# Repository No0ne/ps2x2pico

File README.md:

# ps2x2pico
USB keyboard/mouse to PS/2 interface converter using a Raspberry Pi Pico

| | | | |
|-|-|-|-|

Keyboard only (incl. PC-XT) variant: https://github.com/No0ne/ps2pico  
There is also an alternative ps2pico firmware for the PC-XT and ps2x2pico hardware: [ps2pico-XT-alt.uf2](https://github.com/No0ne/ps2pico/releases/tag/2.2)

Additional excellent documentation by Ray: https://minuszerodegrees.net/keyboard/ps2x2pico.htm

[PicoMiteVGA](https://geoffg.net/picomitevga.html) variant: https://github.com/No0ne/hid2cdc

[PiKVM](https://pikvm.org) integration:
* https://docs.pikvm.org/pico_hid/
* https://docs.pikvm.org/pico_hid_bridge/

[ITX-Llama](https://www.vogons.org/viewtopic.php?t=93480) integration:
https://github.com/eivindbohler/itxllama

# Usage
* Download `ps2x2pico.uf2` from https://github.com/No0ne/ps2x2pico/releases
* Copy `ps2x2pico.uf2` to your Pi Pico by pressing BOOTSEL before pluggging in.
* 3.3V/5V conversion is done using a bi-directional level shifter: https://learn.sparkfun.com/tutorials/bi-directional-logic-level-converter-hookup-guide/
* Afterwards connect a USB keyboard and/or mouse using an OTG-adapter and optional USB hub.
* Also works with wireless keyboards and mice with a dedicated USB receiver.

⚠️ Please note that some older motherboards have non-resettable fuses rated
under 300mA.

**Check the power consumption of your keyboard/mouse/hub first before plugging
in!**

⚠️ Do not assume wire colors will match cables depicted in photos. Double-check
your pinout with a multimeter.

# PS/2 passthru
If you also want to use a real PS/2 keyboard and mouse together with your USB devices you can mount another level shifter on top of the pico. These two ports work as PS/2 inputs and are passed through to the PS/2 output ports.
* GPIO3 LV1 - keyboard data
* GPIO4 LV2 - keyboard clock
* GPIO5 LV - 3.3V pull-up
* GND - GND
* GPIO6 LV3 - mouse data
* GPIO7 LV4 - mouse clock

Don't forget to wire HV to 5V and your PS/2 sockets to power the connected PS/2 devices.

PS/2 passthru is especially useful with the PiKVM [Pico HID](https://docs.pikvm.org/pico_hid/) or [Pico HID Bridge](https://docs.pikvm.org/pico_hid_bridge/) as you can continue using your existing peripherals.  
⚠️ Please note that the [UF2 from PiKVM](https://github.com/pikvm/kvmd/releases) uses different GPIOs due to jumper pins:
* GPIO26 LV1 - keyboard data
* GPIO27 LV2 - keyboard clock
* GPIO16 LV3 - mouse data
* GPIO17 LV4 - mouse clock

Don't forget to wire LV to 3.3V and GND to GND separately as the level shifter does not fit directly on top of the pico. 

# Troubleshooting
You can hook up a USB serial adapter to **GPIO0** for additional debugging output. The serial settings are **115200** baud, **8** data bits and **no parity**. You can also use another Pico running the [pico-uart-bridge](https://github.com/Noltari/pico-uart-bridge) for this.

⚠️ If you have a **YD-RP2040** (see silkscreen on back of board if unsure) and
are not using a USB hub with its own power supply, you need to bridge two pads
of the diode pair near the USB-C port as seen here:

# Build

Install needed libraries and tools:

```sh
sudo apt install cmake gcc-arm-none-eabi build-essential pkg-config libusb-1.0-0-dev libusb-1.0-0
```

Get the Raspberry Pi Pico SDK version 1.5.1:

```sh
git clone https://github.com/raspberrypi/pico-sdk
export PICO_SDK_PATH=/path/to/pico-sdk
cd $PICO_SDK_PATH
git checkout 1.5.1
git submodule update --init
```

Update to the latest TinyUSB release 0.17.0:
```sh
cd $PICO_SDK_PATH/lib/tinyusb
git checkout 0.17.0
```

Generate the UF2 file:
```sh
cd /path/to/ps2x2pico
mkdir build
cd build
cmake ..
make
```

# Case

There are two case versions for this project, one for the hat variant in `freecad/` and one for the level shifter version in `openscad/`.

## Level shifter version

The case is snap fit and doesn't require any fasteners. You can print it as is using `ps2x2pico_case.stl` in your slicer but various customisation options are included in the underlying OpenSCAD model `ps2x2pico_case.scad` should you need them. This allows you to adjust tolerances or clearances of the height of the case and the various holes and support posts.

Note that when opening the case in OpenSCAD the [BOSL2](https://github.com/BelfrySCAD/BOSL2) library is required.

# Resources
* https://github.com/No0ne/ps2pico
* https://wiki.osdev.org/PS/2_Keyboard
* https://wiki.osdev.org/PS/2_Mouse
* https://wiki.osdev.org/Mouse_Input
* https://wiki.osdev.org/%228042%22_PS/2_Controller
* http://www-ug.eecg.toronto.edu/msl/nios_devices/datasheets/PS2%20Keyboard%20Protocol.htm
* http://www-ug.eecg.utoronto.ca/desl/nios_devices_SoC/datasheets/PS2%20Mouse%20Protocol.htm
* Archive.org links for the dead links in the pages above
  * [Main page PS/2 Keyboard Protocol](https://web.archive.org/web/20160414014033if_/http://www.computer-engineering.org/ps2keyboard/)
    * [Scan code set 1](https://web.archive.org/web/20160410193756if_/http://www.computer-engineering.org/ps2keyboard/scancodes1.html)
    * [Scan code set 2](https://web.archive.org/web/20160414030011if_/http://www.computer-engineering.org/ps2keyboard/scancodes2.html)
    * [Scan code set 3](https://web.archive.org/web/20160410184920if_/http://www.computer-engineering.org/ps2keyboard/scancodes3.html)
  * [Main page PS/2 Mouse Protocol](https://web.archive.org/web/20160414013310if_/http://www.computer-engineering.org/ps2mouse/)

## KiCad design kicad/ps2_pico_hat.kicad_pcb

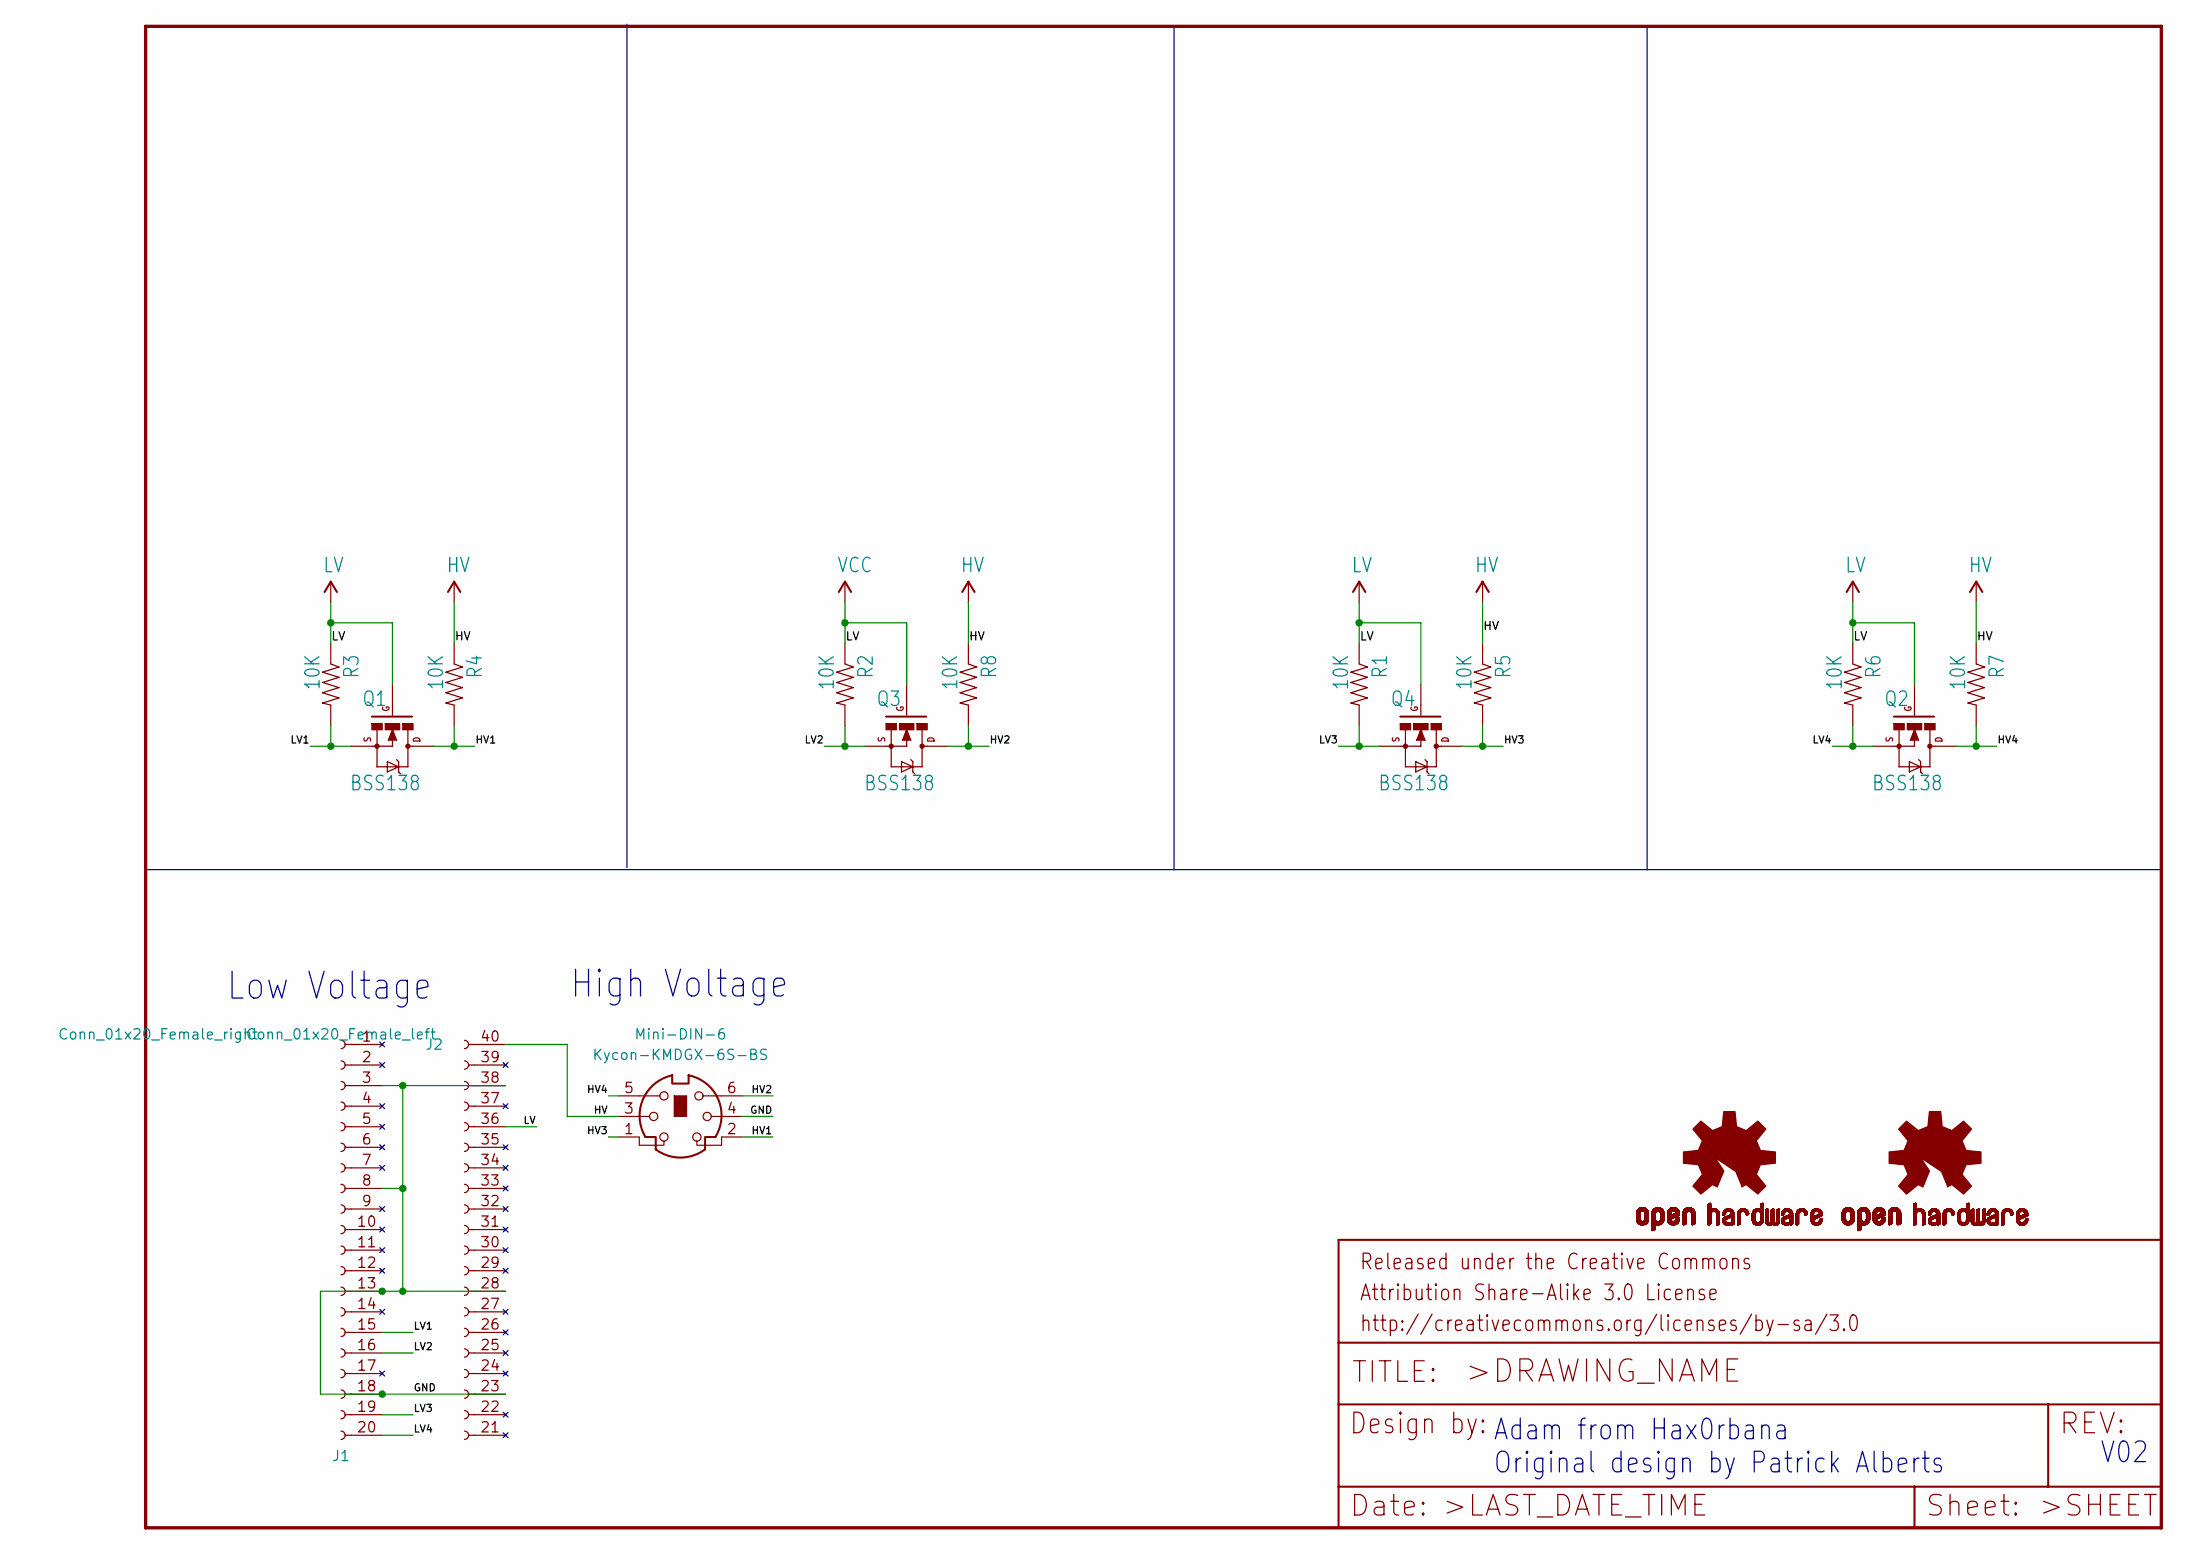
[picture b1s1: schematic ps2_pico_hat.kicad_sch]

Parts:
J1: Conn_01x20_Female_left; PinSocket_1x20_P2.54mm_Vertical
J2: Conn_01x20_Female_right; PinSocket_1x20_P2.54mm_Vertical
LOGO1, LOGO2: OSHW-LOGOS; OSHW-LOGO-S
Mini-DIN-6: Kycon-KMDGX-6S-BS; KMDGX-6S-BS
Q1, Q2, Q3, Q4: BSS138; SOT23-3
R1, R2, R3, R4, R5, R6, R7, R8: 10K; 0603-RES

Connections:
/GND: J1.3 (GND), J1.8 (GND), J1.13 (GND), J1.18 (GND), J2.23 (GND), J2.28 (GND), J2.38 (GND), Mini-DIN-6.4
/HV1: Mini-DIN-6.2, Q1.3 (D), R4.2
/HV2: Mini-DIN-6.6, Q3.3 (D), R8.2
/HV3: Mini-DIN-6.1, Q4.3 (D), R5.2
/HV4: Mini-DIN-6.5, Q2.3 (D), R7.2
/LV1: J1.15, Q1.2 (S), R3.2
/LV2: J1.16, Q3.2 (S), R2.2
/LV3: J1.19, Q4.2 (S), R1.2
/LV4: J1.20, Q2.2 (S), R6.2
HV: J2.40, Mini-DIN-6.3, R4.1, R5.1, R7.1, R8.1
LV: J2.36 (LV), Q1.1 (G), Q2.1 (G), Q3.1 (G), Q4.1 (G), R1.1, R2.1, R3.1, R6.1

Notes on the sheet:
Low Voltage
V02
Adam from Hax0rbana Original design by Patrick Alberts
High Voltage

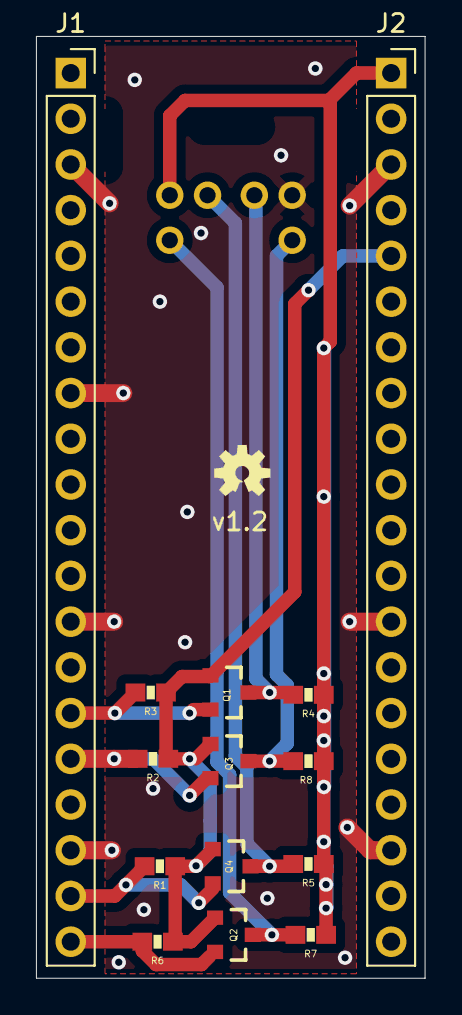
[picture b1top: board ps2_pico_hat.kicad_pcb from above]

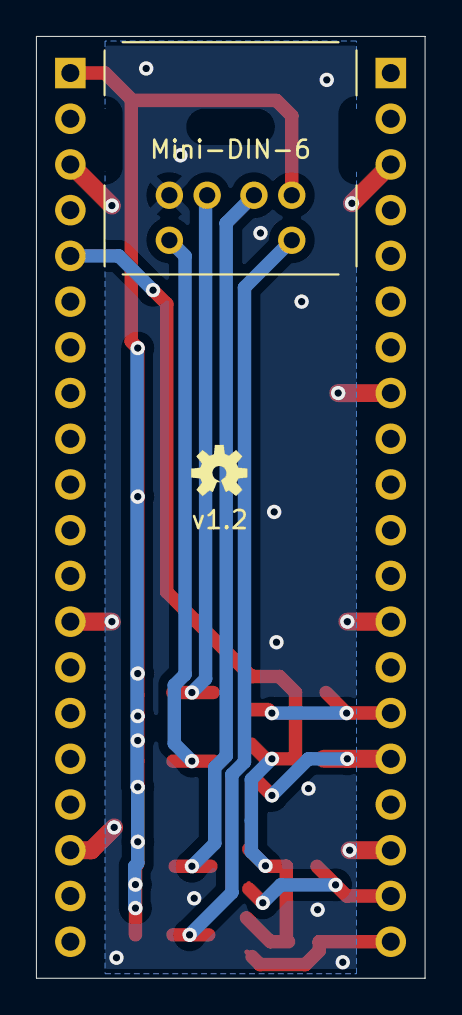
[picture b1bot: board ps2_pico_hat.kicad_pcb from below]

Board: 2 copper layers, 21.6 x 52.3 mm, 17 parts (2 on the bottom side), 11 nets.

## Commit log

2022-08-23 pico_project.py -x -f pio ps2x2pico
2022-08-23 tinyusb
2022-08-24 tinyusb compiled
2022-09-10 blink test
2022-09-10 README.md
2022-09-10 import from ps2pico
2022-09-10 keyboard testing
2022-09-10 keyboard working
2022-09-11 alpha-0.1 - mouse wheel not working + lots of cleanup needed
2022-09-11 alpha-0.2 - mouse wheel working, cleanup still needed
2022-09-13 Logitech Unifying receiver tested
2022-09-13 mousewheel debugging
2022-09-27 updated via ps2pico
2022-11-05 fix timing issue on NuXTv2
2022-11-11 Started implementing a more compatible ps2 mouse emulation
2022-11-12 more compatible ps2 mouse emulation
2022-11-13 ps2ports.pio
2022-11-13 develop sdk
2022-12-04 transmitting via pio
2022-12-07 PIOs tested successfully
2022-12-11 split send & receive state machines
2022-12-13 still something broken
2022-12-14 works on P3B-F
2022-12-14 NuXTv2 working
2022-12-17 receive timing captured from real keyboard
2022-12-17 combine send & receive state machines
2022-12-17 mouse testing
2022-12-18 pio testing nearly finished
2022-12-18 ready for testing
2022-12-22 send 0xaa after blinking
2023-01-26 Working on seperating transciever logic into seperate component.
2023-01-28 More fixes.
2023-01-28 Fixed documentation and removed bad comments.
2023-02-04 fix scroll wheel up represenation
    There are only 4 bit available for scroll wheel movement, not 8 bit.
    Use (0x10 - z) to get the proper 4 bit complement.
2023-02-05 add support for mouse button 4 & 5
2023-04-28 update keyboard prev_rpt atomically
    Modifying previous HID report during parsing of current HID report may
    lead to spurious PS/2 key presses: some HID devices report 2nd key in
    a combo by shifting the report to the right and saving that key in the
    1st report slot, essentially overwriting the 1st key in prev_rpt. The
    1st key in the 2nd slot will be reported once more, as it is missing
    from prev_rpt.
2023-07-23 repeat modifier keys ported from ps2pico
2023-07-29 cleanup
2023-08-02 cleanup in progress
2023-08-02 Squashed commit of the following:
    commit e6f0d15fd73f6b599a8d2a8c85939a060bae5dbc
    Author: No0ne <github@exa.solar>
    Date: Wed Aug 2 20:03:00 2023 +0200
    cleanup in progress
    commit 856ae27570d543a6222a606b0299dd678954a660
    Merge: ef0311e c59f5ef
2023-08-27 updates ported from pikvm picohid
2023-08-27 keyboard and mouse on the same PIO
2023-09-08 PIO version finally working
2023-09-16 better PiKVM integration
2024-01-27 new folder structure
2024-01-28 lock both phys for 1ms
2024-02-16 ps/2 input testing
2024-02-17 keyboard passthru support
2024-02-18 input testing
2024-02-19 keyboard+mouse input
2024-03-02 fix mouse sample rate
2024-03-05 clamp xyz and send rest in next package
2024-03-05 fix mouse movement overflow
2024-03-15 testing 1.0 release
2024-03-15 quick&dirty hid2mac testing
2024-03-25 Add compile-time configuration of mouse sample rate behavior
2024-03-28 prepare 1.0 for pikvm
2024-03-28 200hz mouse optimization
2024-04-19 Note that VBUS == Vin in README diagram
    Some Pi Pico boards silkscreen `Vin` on the `VBUS` pin and mentioning it by that name would make it simpler for novices to assemble their own ps2x2picos.
    ...as well as improve the confidence of people like me who had to read a page like [this](https://randomnerdtutorials.com/raspberry-pi-pico-w-pinout-gpios/) that says "The VBUS (USB Power Input) is t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
2024-04-19 Revert addition of Vin due to contradictory uses
    It turns out that some people use Vin to mean "voltage input" (i.e. VBUS) and some people use it to mean "voltage internal" (i.e. VSYS), so just go back to the old diagram.
2024-04-19 Update README.md for #31
    https://github.com/No0ne/ps2x2pico/issues/31
2024-04-19 Update README.md for #33
2024-04-24 Update README.md for #30
2024-05-12 First working version for scan code set 3 and SGI O2
2024-05-13 Added archive.org links for scan code sets etc.
2024-05-14 scan code set 1 implemented, refactoring
2024-05-14 Fixed type ssc->scs
2024-05-14 resend mechanism corrected
2024-05-16 Fixed USB problems with Dell kb, refactoring, europe keys in set3
2024-05-16 completed scs3 functions, completed scs for europe1/2 keys
2024-05-16 fixed bug of missing e0s for modifiers in scs1 and scs2
2024-05-17 Scan code set 3 fully implemented and tested, scan code set 1 added (untested), minor USB fixes (#39)
    * First working version for scan code set 3 and SGI O2
    * Added archive.org links for scan code sets etc.
    * scan code set 1 implemented, refactoring
    * Fixed type ssc->scs
    * resend mechanism corrected
    * Fixed USB problems with Dell kb, refactoring, europe keys in set3
2024-05-19 allow keyrepat thru host reset, fix ps2phy sent bytes underflow
2024-05-19 fix left ctrl typematic
2024-05-19 revert 0xaa reset response
2024-05-19 restored pikvm compatibility and ctrl+pause key combo
2024-06-07 Make README.md more novice-friendly
    (With the exception of the
    https://commons.wikimedia.org/wiki/File:MiniDIN-6_Connector_Pinout.svg
    diagram from Wikipedia, which is in the public domain, all added diagrams
    and photography are original. All added content is released under the CC0
    to ensure public domain-equivalent status in jurisdictions like Germany
    which don't allow premature release into the public domain.)
2024-06-07 Make README.md more novice-friendly (#44)
2024-06-07 move SVGs to doc folder
2024-06-08 ready to merge
2024-06-08 24 ps2 input (#45)
    * ps/2 input testing
    * keyboard passthru support
    * input testing
    * keyboard+mouse input
    * fix mouse sample rate
    * clamp xyz and send rest in next package
2024-06-10 fix issue #42 timing
2024-06-14 #24 PS2 input repeating
2024-07-27 fix PiKVM compile warnings
2024-08-07 disable #36 experiment
2024-09-30 docs: improved documentation for compiling and disambiguated comments about GPIO numbers vs pin numbers
2024-10-13 cad: added pico hat to implement the hardware for this project
2024-10-15 feat: added CAD model for a 3D printed case
2024-10-15 doc: added photos of pico hat and cases
2024-10-19 docs: added version number to PCB
2024-11-05 pre-1.3: mouse now runs in report mode
2024-11-07 Improved documentation for the hat
    - Changed label on J3 to J2
    - Added missing links to components
    - Regenerated the iBOM with links to buy components
    - Removed backup files committed in error
2024-11-14 pre-1.3: mouse now runs in report mode with Pico-SDK 1.5.1
2024-11-15 PS/2 passthru doc
2024-11-16 prepare ITX-Llama integration
2024-11-19 fix 8bitdo keyboard
2024-11-20 report mode for every device
2024-11-20 report mode fixes
2024-11-21 NKRO testing
2024-11-22 Apple Keyboard sends extra byte for FN + eject
2024-11-27 Compiling pre-2.0 with PicoSDK-2.1.0
2024-11-28 USB replugging still doesn't work with PicoSDK-2.1.0
2024-12-05 testing PIO usb ports
2024-12-05 remove mouse acpan
2024-12-05 update README.md build section
2024-12-05 release version 2.0
2024-12-05 dual USB mode
2024-12-12 fix NKRO for keyboards with QMK firmware
2024-12-14 Fix compiler error: usbin.c
2024-12-15 release version 2.1
2025-03-04 test fix for #73 and #76
2025-07-26 prepare 3.0
2026-02-09 feat: Add level shift OpenSCAD case
2026-02-12 feat: Add level shift OpenSCAD case (#94)
    Thanks for that!
2026-04-02 Fix build with C23
    C23 (the fault in GCC 15) interprets an empty argument list as no
    arguments rather than unspecified and arbitrary arguments. Callbacks now
    have to actually match the declared type.

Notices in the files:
kicad/ps2_pico_hat.kicad_sch:
http://creativecommons.org/licenses/by-sa/3.0
Released under the Creative Commons
